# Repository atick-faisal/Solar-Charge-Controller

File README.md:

# `Solar-Charge-Controller` 

## Specifications

 ##### Battery Voltage : 12V
 ##### VR = 14.4V, ARV = 13.0V
 ##### LVD = 10.8V, LRV = 12.5V

## Schematic

## Tuning the Circuit
<p align="center">
  
  <br>
  
</p>

## Simulation Result

## License

This work is licensed under `Apache License 2.0`

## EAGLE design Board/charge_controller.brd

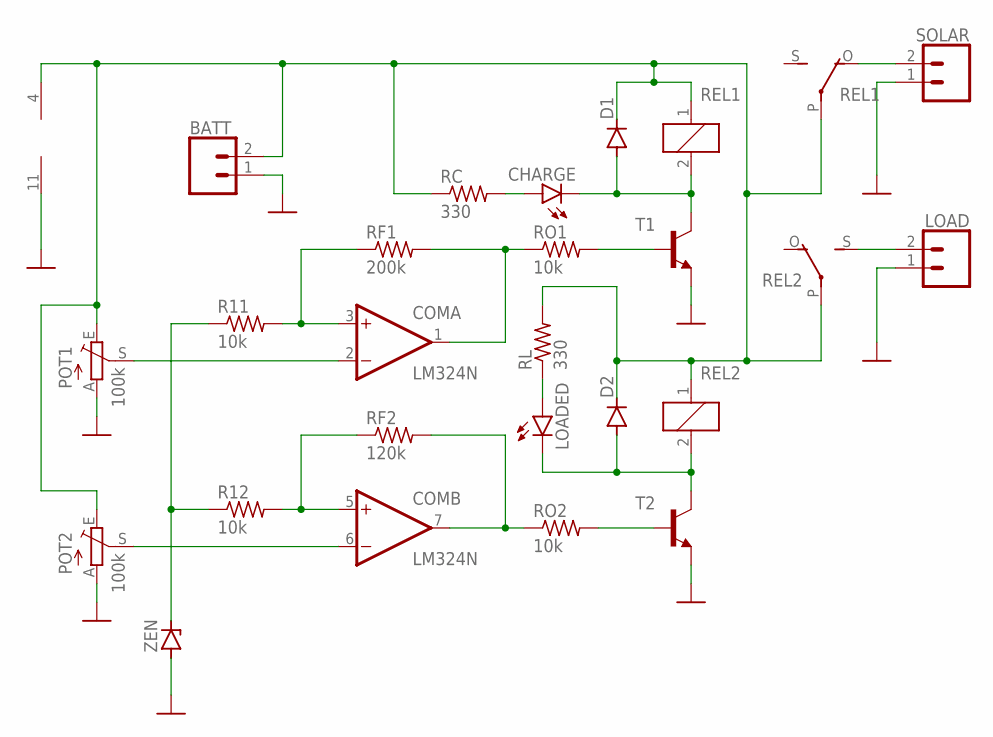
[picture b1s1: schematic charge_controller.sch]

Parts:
BATT: CONN_02PTH4; 1X02_XTRA_BIG
CHARGE: LED5MM
COM: LM324N; DIL14
D1, D2: 1N4148DO35-7; DO35-7
LOAD: CONN_02PTH4; 1X02_XTRA_BIG
LOADED: LED5MM
POT1, POT2: 100k; CT6
R11, R12: 10k; 0207/10
RC: 330; 0207/10
REL1, REL2: G5L; G5LE
RF1: 200k; 0207/10
RF2: 120k; 0207/10
RL: 330; 0207/10
RO1, RO2: 10k; 0207/10
SOLAR: CONN_02PTH4; 1X02_XTRA_BIG
T1, T2: BF393-NPN-TO92-CBE; TO92-CBE
ZEN: BZD23; SOD81

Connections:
GND: BATT.1, COM.11 (V-), LOAD.1, POT1.A, POT2.A, SOLAR.1, T1.E, T2.E, ZEN.A
unnamed: COM.3 (+IN), R11.2, RF1.1
unnamed: COM.5 (+IN), R12.2, RF2.1
unnamed: COM.2 (-IN), POT1.S
unnamed: COM.6 (-IN), POT2.S
unnamed: R11.1, R12.1, ZEN.C
unnamed: COM.7 (OUT), RF2.2, RO2.1
unnamed: COM.1 (OUT), RF1.2, RO1.1
unnamed: RO1.2, T1.B
unnamed: RO2.2, T2.B
unnamed: D2.A, LOADED.K (C), REL2.2, T2.C
unnamed: REL1.O, SOLAR.2
unnamed: CHARGE.K (C), D1.A, REL1.2, T1.C
unnamed: LOAD.2, REL2.S
unnamed: BATT.2, COM.4 (V+), D1.C, D2.C, POT1.E, POT2.E, RC.1, REL1.1, REL1.P, REL2.1, REL2.P, RL.2
unnamed: CHARGE.A, RC.2
unnamed: LOADED.A, RL.1

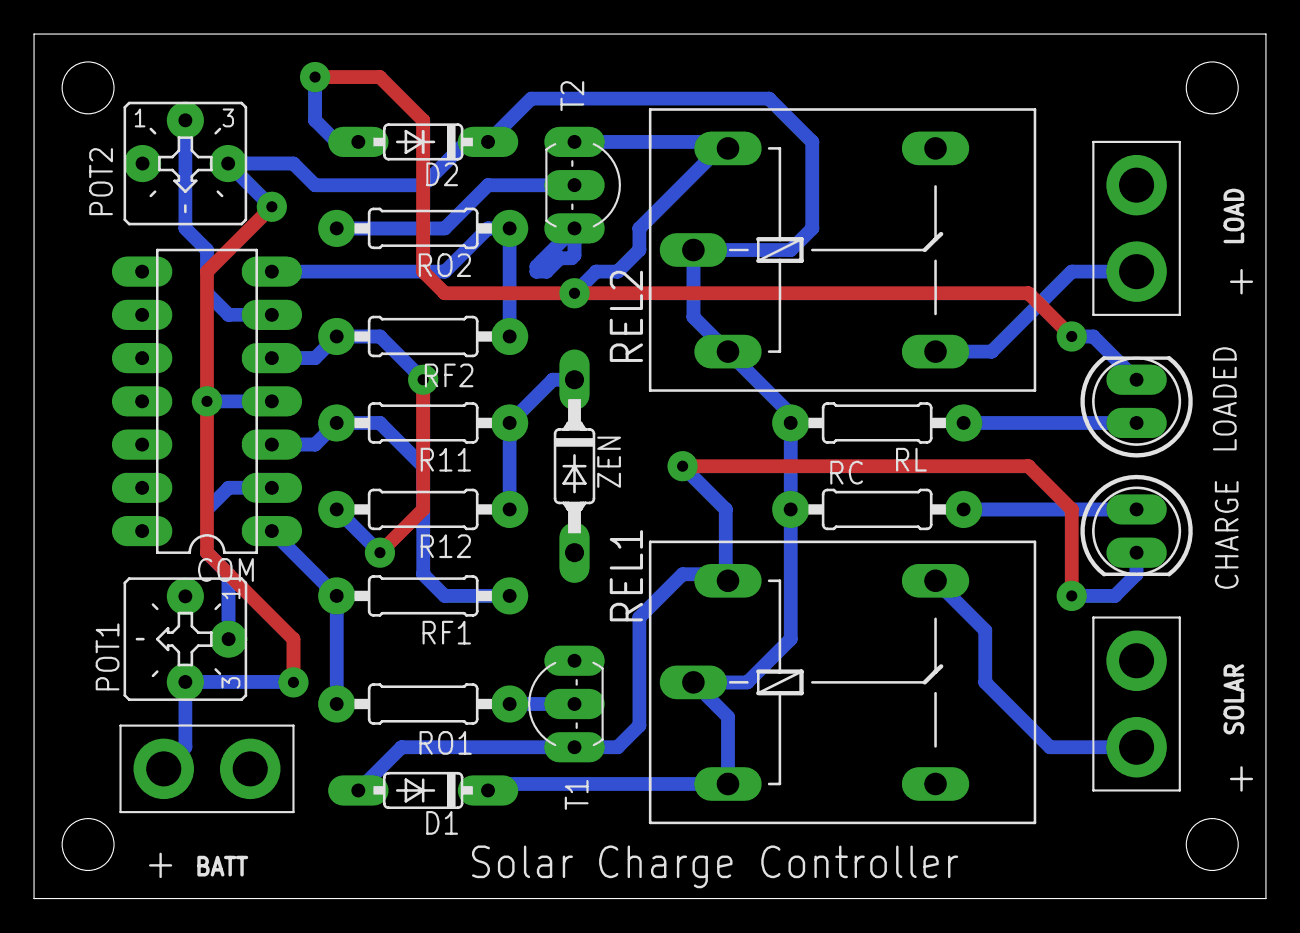
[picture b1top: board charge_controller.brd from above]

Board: 2 copper layers, 72.4 x 50.8 mm, 23 parts (0 on the bottom side), 17 nets.

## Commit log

2019-10-12 added logo
2019-10-12 added schematic
2019-10-12 added simulation
2019-10-13 design changed

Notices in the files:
README.md:
License: Apache 2.0
parts and their libraries:
atick_connector: Licensing: Creative Commons ShareAlike 4.0 International - https://creativecommons.org/licenses/by-sa/4.0
